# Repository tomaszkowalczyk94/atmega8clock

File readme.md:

# ATmega8 Digital LED Clock ⏰

|  |

A custom-built, DIY digital clock powered by an **ATmega8** microcontroller and a 4-digit 7-segment green LED display. This project involves a custom perfboard circuit, transistor-based display multiplexing, and a fully custom 3D-printed enclosure designed in FreeCAD.

## 🌟 Features
* **Microcontroller:** Atmel ATmega8 
* **Display:** 0.56" 4-Digit 7-Segment LED display with colons/dots (LED4-AF-05643FG-B PBF).
* **Multiplexing:** Utilizes BC547 NPN transistors for switching the common anodes.
* **Custom Enclosure:** 3D printed case and lid, originally modeled in FreeCAD.
* **Programming:** Flashed via a USBAsp programmer using Arduino IDE.

---

## 🛠️ Hardware & Components

* **1x ATmega8** Microcontroller
* **1x LED4-AF-05643FG-B PBF** (4-Digit 7-Segment Display, 0.56", Green, Common Anode)
* **5x BC547 NPN Transistors** (Used to drive the common anodes)
* **Resistors** (For base current limiting on the transistors and segment current limiting)
* **USBAsp Programmer** (For flashing the ATmega8)
* Universal perfboard/stripboard

---

## 🔌 Circuit & Pinout

The display requires multiplexing. The **Common Anodes** are driven by the ATmega8 via BC547 NPN transistors (which conduct when a high signal is applied to the base). The **Cathodes** are connected directly to the ATmega8 digital pins. 

### Anode Connections (via BC547 Transistors)
| Display Pin | ATmega8 Pin (Arduino IDE) | Function |
| :--- | :--- | :--- |
| **14** | Digital Pin 13 | DIGIT 1 |
| **11** | Digital Pin 10 | DIGIT 2 |
| **10** | Digital Pin 9 | DIGIT 3 |
| **7** | Digital Pin 6 | Colon / Dots (UC, LC) |
| **6** | Digital Pin 5 | DIGIT 4 |

### Cathode Connections (Direct to ATmega8)
| Display Pin | ATmega8 Pin (Arduino IDE) | Segment |
| :--- | :--- | :--- |
| **13** | Digital Pin 12 | Segment A |
| **9** | Digital Pin 8 | Segment B |
| **4** | Digital Pin 3 | Segment C |
| **2** | Digital Pin 1 | Segment D |
| **1** | Digital Pin 0 | Segment E |
| **12** | Digital Pin 11 | Segment F |
| **5** | Digital Pin 4 | Segment G |
| **3** | Digital Pin 2 | Dot (DP / OP) |
| **8** | Digital Pin 7 | Colon (UC, LC) |

---

## 📦 3D Printed Enclosure

The repository includes custom 3D models for the clock's housing.
* **`case.FCStd`**: The original FreeCAD project file. Use this if you want to modify the dimensions or design.
* **`case-PartBody.stl`**: The main body of the enclosure, ready for slicing and 3D printing.
* **`case-wieczkoThickness001.stl`**: The back lid/cover for the enclosure.

*Tip: Print with standard PLA/PETG. No special supports are required if oriented face-down.*

---

## 💻 Software & Programming

The code for this project was written in the Arduino IDE and leverages basic multiplexing logic to illuminate the 7-segment display. 

**Flashing the ATmega8:**
1. You will need a **USBAsp** programmer.
2. Install the necessary drivers using [Zadig](https://zadig.akeo.ie/).
3. Connect the USBAsp to the ATmega8 via the ISP headers.
4. In Arduino IDE, select the ATmega8 board, set the programmer to "USBAsp", and click **"Upload Using Programmer"**.

*Helpful resources for programming raw AVR chips:*
* [Majsterkowo: Programming microcontrollers with USBAsp (Polish)](https://majsterkowo.pl/programowanie-mikrokontrolerow-za-pomoca-programatora-usbasp/)
* [YouTube Tutorial](https://www.youtube.com/watch?v=X01Nhq8TeY0&t=58s)

---

## 📸 Gallery

| Circuit Design | 
| :---: 
|  |

| Prototype | 
| :---: 
|  |

| Final electronic board | 
| :---: 
|  |

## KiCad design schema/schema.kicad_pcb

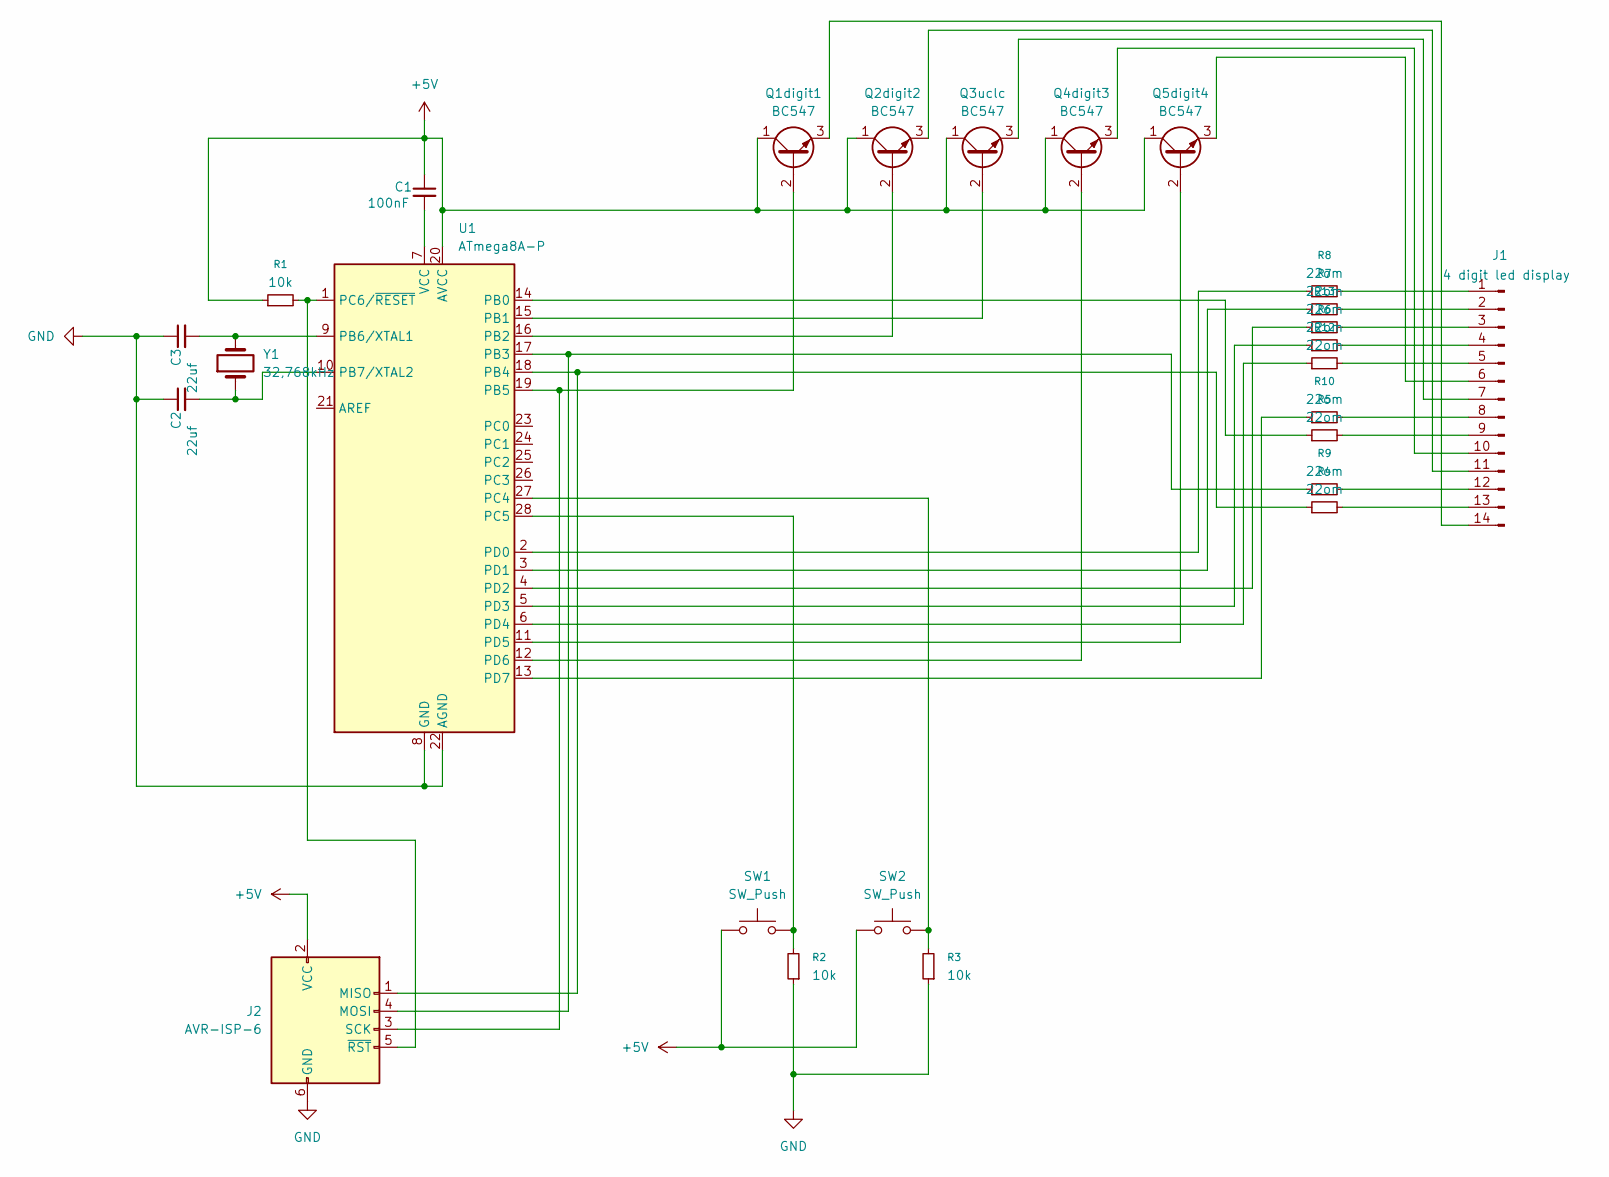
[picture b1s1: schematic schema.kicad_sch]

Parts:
C1: 100nF
C2, C3: 22uf
J1: 4 digit led display; Hirose_DF13-14P-1.25DSA_1x14_P1.25mm_Vertical
J2: AVR-ISP-6
Q1digit1, Q2digit2, Q3uclc, Q4digit3, Q5digit4: BC547; TO-92_Inline
R1, R2, R3: 10k
R4, R5, R6, R7, R8, R9, R10, R12, R13: 22om
SW1, SW2: SW_Push
U1: ATmega8A-P; DIP-28_W7.62mm
Y1: 32,768kHz

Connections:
+5V: C1.1, J2.2 (VCC), Q1digit1.1 (C), Q2digit2.1 (C), Q3uclc.1 (C), Q4digit3.1 (C), Q5digit4.1 (C), R1.1, SW1.1, SW2.1, U1.20 (AVCC); also elsewhere on the board
GND: C2.1, C3.1, J2.6 (GND), R2.1, R3.1, U1.8 (GND), U1.22 (AGND)
unnamed: J1.1, R8.2
unnamed: J1.2, R7.2
unnamed: J1.3, R13.2
unnamed: J1.4, R6.2
unnamed: J1.5, R12.2
unnamed: J1.6, Q5digit4.3 (E)
unnamed 8: J1.7, Q3uclc.3 (E); also elsewhere on the board
unnamed: J1.8, R10.2
unnamed: J1.9, R5.2
unnamed: J1.10, Q4digit3.3 (E)
unnamed: J1.11, Q2digit2.3 (E)
unnamed: J1.12, R9.2
unnamed: J1.13, R4.2
unnamed: J1.14, Q1digit1.3 (E)
unnamed: J2.1 (MISO), R4.1, U1.18 (PB4)
unnamed: J2.4 (MOSI), R9.1, U1.17 (PB3)
unnamed: J2.3 (SCK), Q1digit1.2 (B), U1.19 (PB5)
unnamed: J2.5 (~RST), R1.2, U1.1 (PC6/~RESET)
unnamed: Q2digit2.2 (B), U1.16 (PB2)
unnamed 21: Q3uclc.2 (B), U1.15 (PB1); also elsewhere on the board
unnamed: Q4digit3.2 (B), U1.12 (PD6)
unnamed: Q5digit4.2 (B), U1.11 (PD5)
unnamed: R5.1, U1.14 (PB0)
unnamed: C3.2, U1.9 (PB6/XTAL1), Y1.2
unnamed: C2.2, U1.10 (PB7/XTAL2), Y1.1
unnamed: R3.2, SW2.2, U1.27 (PC4)
unnamed: R2.2, SW1.2, U1.28 (PC5)
unnamed: R8.1, U1.2 (PD0)
unnamed: R7.1, U1.3 (PD1)
unnamed: R13.1, U1.4 (PD2)
unnamed: R6.1, U1.5 (PD3)
unnamed: R12.1, U1.6 (PD4)
unnamed: R10.1, U1.13 (PD7)
unnamed: C1.2, U1.7 (VCC)

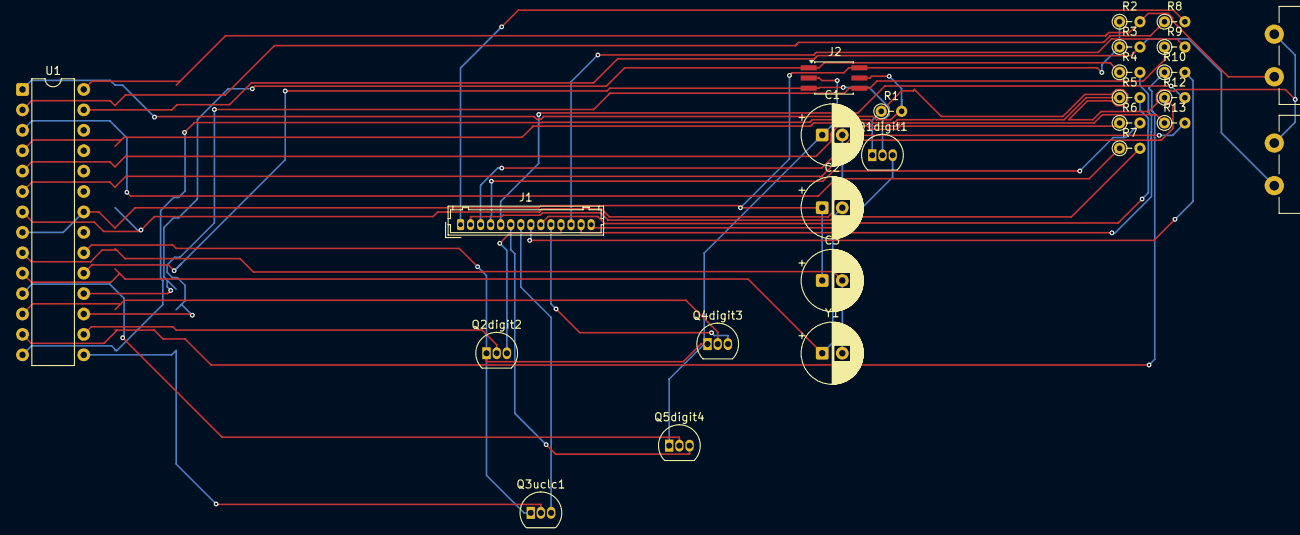
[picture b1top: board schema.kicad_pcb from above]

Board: 2 copper layers, 26 parts (0 on the bottom side), 36 nets.

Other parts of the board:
Q3uclc1: BC547; TO-92_Inline

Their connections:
+5V: Q3uclc1.1 (C); also elsewhere on the board
unnamed 8: Q3uclc1.3 (E); also elsewhere on the board
unnamed 21: Q3uclc1.2 (B); also elsewhere on the board

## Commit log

2025-09-28 init
